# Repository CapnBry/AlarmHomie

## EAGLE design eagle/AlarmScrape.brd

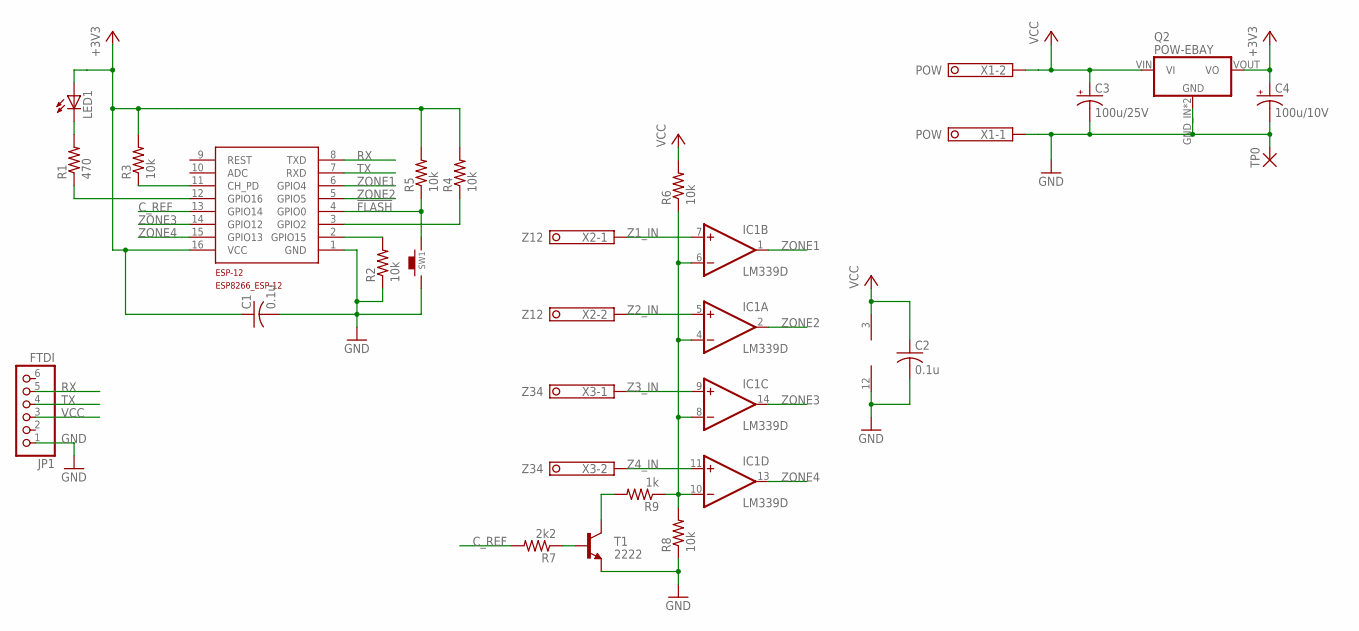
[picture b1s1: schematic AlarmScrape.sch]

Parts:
C1, C2: 0.1u; C0805
C3: 100u/25V; E2,5-6
C4: 100u/10V; E2,5-6
ESP-12: ESP8266_ESP-12; ESP8266-ESP12
IC1: LM339D; SO14
JP1: FTDI; 1X06
LED1: LEDCHIPLED_0805; CHIPLED_0805
Q2: POW-EBAY; POW-BUCK-EBAY
R1: 470; R0805
R2, R3, R4, R5, R6, R8: 10k; R0805
R7: 2k2; R0805
R9: 1k; R0805
SW1: FLASH; TACT-4X3
T1: 2222; SOT23-3
TP0: THROUGH-HOLE; PAD-032
X1: POW; 1751248
X2: Z12; 1751248
X3: Z34; 1751248

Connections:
!FLASH: ESP-12.4 (GPIO0), R5.1, SW1.P1
+3V3: C1.1, C4.+, ESP-12.16 (VCC), LED1.A, Q2.VOUT (VO), R3.2, R4.2, R5.2
C_REF: ESP-12.13 (GPIO14), R7.2
GND: C1.2, C2.2, C3.-, C4.-, ESP-12.1 (GND), IC1.12 (GND), JP1.1, Q2.GND_IN (GND), Q2.GND_OUT (GND), R2.1, R8.1, SW1.P0, T1.2 (E), TP0.P, X1.1
unnamed: ESP-12.12 (GPIO16), R1.1
unnamed: ESP-12.11 (CH_PD), R3.1
unnamed: ESP-12.2 (GPIO15), R2.2
unnamed: LED1.C, R1.2
unnamed: ESP-12.3 (GPIO2), R4.1
unnamed: R7.1, T1.1 (B)
unnamed: IC1.4 (-IN), IC1.6 (-IN), IC1.8 (-IN), IC1.10 (-IN), R6.1, R8.2, R9.1
unnamed: R9.2, T1.3 (C)
RX: ESP-12.8 (TXD), JP1.5
TX: ESP-12.7 (RXD), JP1.4
VCC: C2.1, C3.+, IC1.3 (V+), JP1.3, Q2.VIN (VI), R6.2, X1.2
Z1_IN: IC1.7 (+IN), X2.1
Z2_IN: IC1.5 (+IN), X2.2
Z3_IN: IC1.9 (+IN), X3.1
Z4_IN: IC1.11 (+IN), X3.2
ZONE1: ESP-12.6 (GPIO4), IC1.1 (OUT)
ZONE2: ESP-12.5 (GPIO5), IC1.2 (OUT)
ZONE3: ESP-12.14 (GPIO12), IC1.14 (OUT)
ZONE4: ESP-12.15 (GPIO13), IC1.13 (OUT)

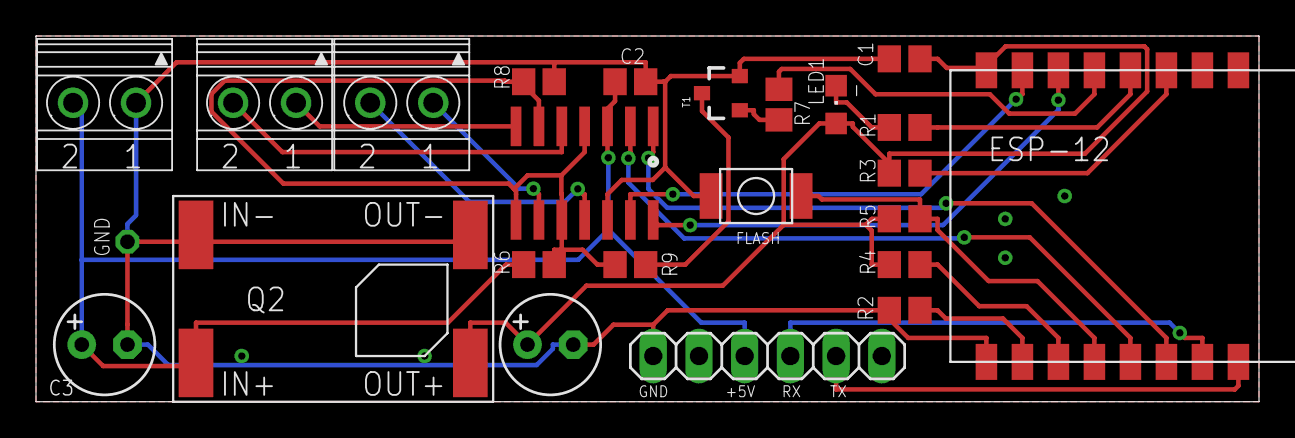
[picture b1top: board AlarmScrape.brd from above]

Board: 2 copper layers, 67.9 x 20.3 mm, 24 parts (0 on the bottom side), 23 nets.

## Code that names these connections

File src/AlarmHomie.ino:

#include <vector>
#include <Homie.h>

#define DPIN_ZONE1 4		// D2 on NodeMCU
#define DPIN_ZONE2 5		// D1 on NodeMCU
#define DPIN_ZONE3 12       // D6 on NodeMCU
#define DPIN_ZONE4 13       // D7 on NodeMCU
#define DPIN_COMP_REF 14    // D5 on NodeMCU

#define RETRIGGER_INTERVAL 10000U // how often a state change can occur (ms)

HomieNode alarmNode("alarm", "multizone-alarm");

class AlarmPin
{
public:
  enum PinState { Unknown, Normal, Triggered, Fault };

  AlarmPin(uint8_t pin, const char* name)
    : _name(name), _pin(pin),
    _aboveLow(0), _aboveHigh(0),
    _lastState(Unknown), _lastStateChange(0), _stateDiffCnt(0)
  {
    // Some pins should already be pulled up to prevent booting to flash mode
    if (pin == 0 || pin == 2)
      pinMode(pin, INPUT);
    else
      pinMode(pin, INPUT_PULLUP);
  }

  void checkLow()
  {
    _aboveLow = digitalRead(_pin);
  }

  void checkHigh()
  {
    _aboveHigh = digitalRead(_pin);
  }

  void update()
  {
    PinState newState;
    if (_aboveHigh)
      newState = PinState::Triggered;  // Above High reference
    else if (_aboveLow)
      newState = PinState::Normal; // Low < x < High
    else
      // Below the Low reference
      // and High < x < Low (Impossible)
      newState = PinState::Fault;

    if (_lastState == PinState::Unknown ||
      ((_lastState != newState) && (millis() - _lastStateChange > RETRIGGER_INTERVAL)))
    {
      ++_stateDiffCnt;
      // Must be in this new state more than once before we consider it a transition
      if (_stateDiffCnt > 1)
      {
        _stateDiffCnt = 0;
        _lastState = newState;
        _lastStateChange = millis();
        Homie.setNodeProperty(alarmNode, _name, PinStateStr(_lastState), false);
      }
    }
    else
      _stateDiffCnt = 0;
  }

  static const char* PinStateStr(PinState p)
  {
    switch (p)
    {
    case PinState::Unknown:
      return "null"; break;
    case PinState::Normal:
      return "normal"; break;
    case PinState::Triggered: 
      return "triggered"; break;
    case PinState::Fault: 
      return "fault"; break;
    }
    return NULL;
  }

private:
  const char* _name;
  uint8_t _pin;
  uint8_t _aboveLow;
  uint8_t _aboveHigh;
  PinState _lastState;
  uint32_t _lastStateChange;
  uint8_t _stateDiffCnt;
};

static std::vector<AlarmPin *> pins;

bool checkAlarm()
{
  const uint32_t UPDATE_INTERVAL = 200U;
  static uint32_t lastUpdate;

  if (millis() - lastUpdate > UPDATE_INTERVAL)
  {
    // Check for above high reference
    for (uint8_t i = 0; i < pins.size(); ++i)
      pins[i]->checkHigh();

    // Turn on the REF transistor to lower reference voltage
    digitalWrite(DPIN_COMP_REF, HIGH);
    delay(1);

    // Check for above low reference
    for (uint8_t i = 0; i < pins.size(); ++i)
    {
      pins[i]->checkLow();
      pins[i]->update();
    }

    // Turn off the REF transistor for the next measurement
    digitalWrite(DPIN_COMP_REF, LOW);
    lastUpdate = millis();
    return true;
  }
  return false;
}


void setupHandler()
{
  digitalWrite(DPIN_COMP_REF, LOW);
  pinMode(DPIN_COMP_REF, OUTPUT);

  pins.push_back(new AlarmPin(DPIN_ZONE1, "zone1"));
  pins.push_back(new AlarmPin(DPIN_ZONE2, "zone2"));
  pins.push_back(new AlarmPin(DPIN_ZONE3, "zone3"));
  pins.push_back(new AlarmPin(DPIN_ZONE4, "zone4"));
}

void loopHandler()
{
  checkAlarm();
}

void setup() {
  // Blink the LED a while to allow the serial port time to connect
  pinMode(BUILTIN_LED, OUTPUT);
  for (unsigned char i=0; i<25; ++i)
  {
    digitalWrite(BUILTIN_LED, LOW);
    delay(100);
    digitalWrite(BUILTIN_LED, HIGH);
    delay(100); 
  }

  Homie.setFirmware("alarm-homie", "1");
  Homie.setSetupFunction(setupHandler);
  Homie.setLoopFunction(loopHandler);
  Homie.registerNode(alarmNode);
  Homie.setup();
}

void loop() {
  Homie.loop();
}

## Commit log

2016-05-05 :circus_tent: Added .gitattributes
2016-05-05 Import
2016-05-05 Untabify source
2016-05-05 Remove DHT measuring stuff
2016-05-08 PCB rev 2
    -- Added LED
    -- Removed !RESET pullup
    -- Disconnected RTS from GP0 and !RESET
    -- FTDI VCC now connected to VIN instead of 3.3V

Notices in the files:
parts and their libraries:
SparkFun: Licensing: CC v3.0 Share-Alike You are welcome to use this library for commercial purposes.
